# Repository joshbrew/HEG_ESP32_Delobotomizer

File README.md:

# HEG ESP32 - Delobotomizer Edition

Official repository for the HEGduino V2 Delobotomizer firmware, software, and designs.

### [WebApp: Brains@Play](https://app.brainsatplay.com)
- This will replace the original software and is MUCH more robust, we are still doing a lot of legwork to get all of the quality of life features we want into it but welcome to the new multi-bci community framework for the web! 
- Chrome only for desktop, works on Android and in VR. 
- Find the install button via the settings button in the top right of the browser.
### [Getting Started (click me)](https://github.com/moothyknight/HEG_ESP32_Delobotomizer/blob/main/Guides/GettingStarted.md)
### [Updating Your Device](https://github.com/moothyknight/HEG_ESP32_Delobotomizer/blob/main/Guides/Updating.md)
### [Whitepaper](https://github.com/moothyknight/HEG_ESP32_Delobotomizer/blob/main/Guides/Open%20Source%20HEG_FNIRS%20Whitepaper.pdf)
### [Old Progressive Web App (no longer updated)](https://hegalomania.netlify.app) 
- Original webapp demo, use via Chrome for Serial USB support. Use BLE mode if the USB device is not recognized in browser, this is a known issue. If that fails use the web server with the device in WiFi mode.

### If your browser won't identify the USB connection, try installing the VCP for Windows (or Mac) drivers here: https://www.silabs.com/developers/usb-to-uart-bridge-vcp-drivers

## Firmware

The Firmware folder contains a .bin file that you can use via the on-board web interface to update the device. There are Arduino libraries and firmware code files for custom code, you will need the ESP32 module additionally for Arduino.

Simply connect to the wifi network named "My_HEG" when the device is powered up with password "12345678"

In your preferred browser, enter "192.168.4.1" into the address bar. You should see an interface show up. Click on the Update button to go to the update page.

Now follow the instructions on screen to browse for the .bin folder that you may download from this repo. Wait for it to finish uploading then reconnect to the HEG after that's taken care of if it does not do it automatically. Voila!

## Progressive Web App (WIP): https://hegalomania.netlify.app

Our new preferred method for using the HEG, a state of the art Progressive Web App! 

Open this link to use your HEG in a Chrome browser or Android for instant access to using your device. This is being updated to a React app with a more familiar UI and a more concise code base to expand from.

You may install it locally on desktop or mobile as well just like any app and create desktop shortcuts. For desktop open the settings bar in Chrome and click "Install HEG Alpha." The USB mode only works in chrome right now as it is a development feature. You can enable this feature by going to chrome://flags and enabling the "Experimental Web Platform features" flag. For mobile it should prompt you to install, if not find the install button in your chrome settings menu on mobile.

## Boot routine

The newer firmware contains a new boot-up routine for making it easier to identify streaming modes on the device. It will flash when powered up to indicate which mode it's in.

On boot:
* Two fast blinks: BLE mode
* Three fast blinks: WIFI mode
* Four fast blinks: Bluetooth Classic (Serial) mode

The button on the newer devices puts your device to sleep. There will be a switch added next to control device settings.

Since your device is covered in tape this will help you find the reset button if I didn't mark it for you:

## Device Commands (accessible via app (Send Command button) or serial monitor)

* 't' - Turn sensor ON (automatic)
* 'f' - Turn sensor OFF, device will go to sleep after 10min of inactivity
* 'b' - BLE mode toggle. Toggles back to WiFi mode.
* 'B' - Bluetooth Serial toggle. Toggles back to WiFi mode.
* 'W' - Reset WiFi credentials (if it won't connect to your router)
* 'R' - Reboot device
* 'S' - Enter deep sleep mode e.g. to save battery
* 'u' - USB only output mode (no wireless signals)
* 'o' - Fast output mode (<20 byte packets for Android Web BLE)
* 'L' - External LED mode, configured for pins 12 and 14 to run LEDs and be sampled.
* 'N' - Toggle SPO2 output (experimental, not working properly yet)
* 'D' - Toggle Debug output (for using Arduino's graphing)
* 'e' - Toggle exposure settings: slow, fast, and default. default has the slowest output rate but samples faster than slow mode with more averaging.
* 'l' - Toggle LED protocols in this order: Ambient,IR,2 IR (AMBIENT, LED2, LED1+2); Red,IR,2 IR (LED3, LED2, LED1+2), Red = IR (LED1, LED2, AMB), or Default (LED3,LED2,AMBIENT)
* 'X' - DC filter toggle
* 'F' - Digital filter toggle
Note, use the first setting with the command 'l' if your red LED is underperforming. This will make the software compare Ambient and IR, and optional both IR LEDs for extra strength. For some reason the red output is not as consistent for some people.

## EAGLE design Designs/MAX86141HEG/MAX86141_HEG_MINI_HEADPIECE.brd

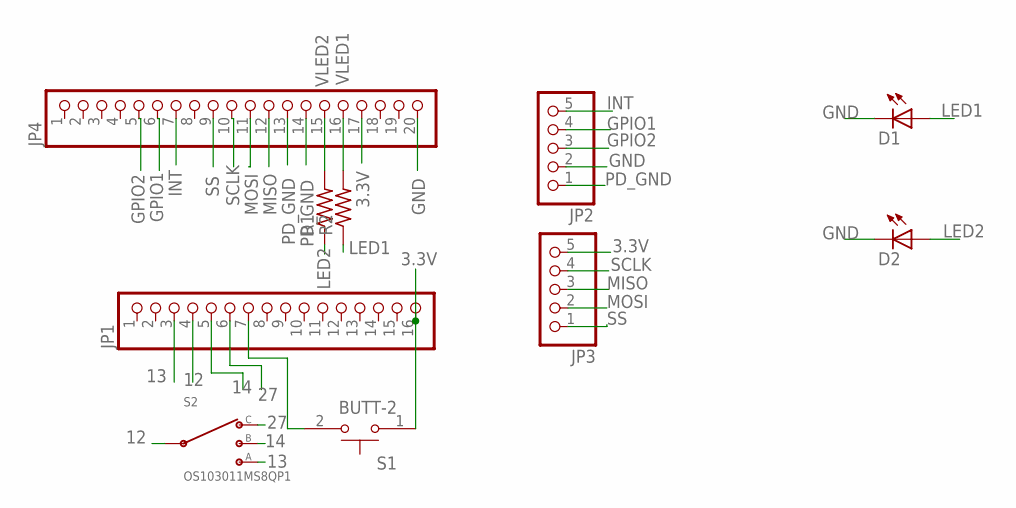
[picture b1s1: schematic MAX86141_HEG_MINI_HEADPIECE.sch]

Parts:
D1, D2: LED1206; LED-1206
JP1: PINHD-1X16; 1X16
JP2, JP3: PINHD-1X5; 1X05
JP4: PINHD-1X20; 1X20
R1, R2: R-US_0204/5; 0204/5
S1: BUTT-2; SW_BUTT-2
S2: OS103011MS8QP1; OS102011MS8QP1

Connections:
3.3V: JP1.16, JP3.5, JP4.17, S1.1
12: JP1.4, S2.2 (C)
13: JP1.3, S2.1
14: JP1.5, S2.3 (2)
27: JP1.6, S2.4 (3)
GND: D1.C, D2.C, JP2.2, JP4.20
GPIO1: JP2.4, JP4.6
GPIO2: JP2.3, JP4.5
INT: JP2.5, JP4.7
LED1: D1.A, R2.1
LED2: D2.A, R1.1
MISO: JP3.3, JP4.12
MOSI: JP3.2, JP4.11
unnamed: JP1.7, S1.2
PD_GND: JP2.1, JP4.13, JP4.14
SCLK: JP3.4, JP4.10
SS: JP3.1, JP4.9
VLED1: JP4.16, R2.2
VLED2: JP4.15, R1.2

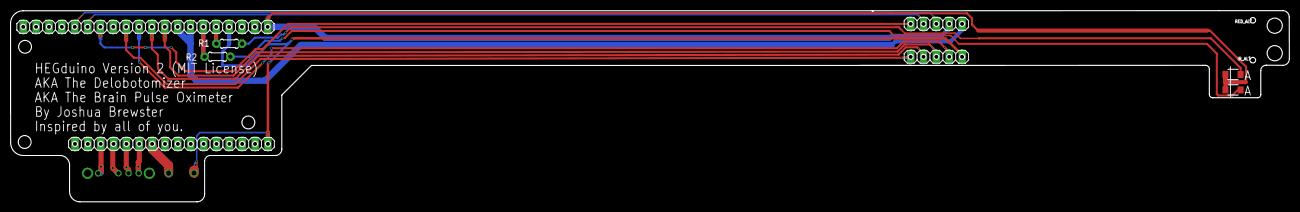
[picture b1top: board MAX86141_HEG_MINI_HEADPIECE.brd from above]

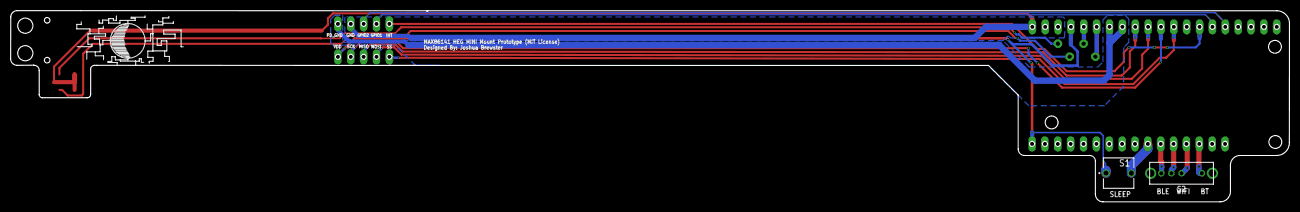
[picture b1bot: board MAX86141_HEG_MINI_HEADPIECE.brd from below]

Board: 2 copper layers, 252.5 x 37.7 mm, 10 parts (2 on the bottom side), 19 nets.

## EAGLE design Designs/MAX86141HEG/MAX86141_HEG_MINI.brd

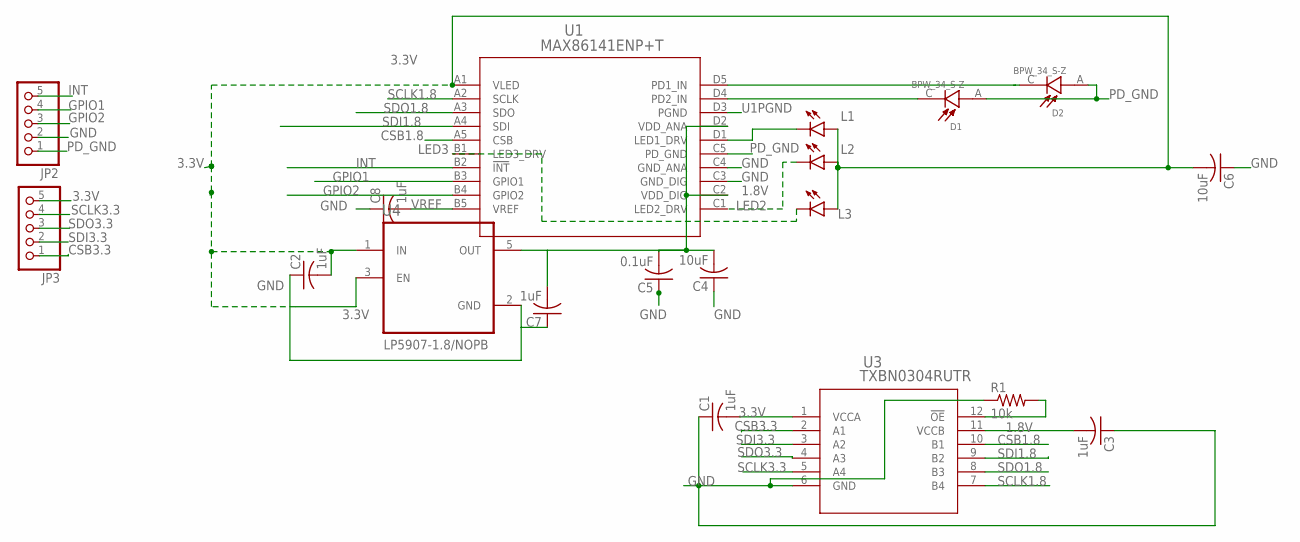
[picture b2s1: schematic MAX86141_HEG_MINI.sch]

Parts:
C1, C2, C3, C7, C8: 1uF; C0402
C4, C6: 10uF; C0402
C5: 0.1uF; C0402
D1, D2: BPW_34_S-Z; DIO_BPW_34_S-Z
JP2, JP3: PINHD-1X5; 1X05
L1, L2, L3: LEDCHIPLED_1206; CHIPLED_1206
R1: 10k; R0402
U1: MAX86141ENP+T; 21-100134_N201A2-1_MXM
U3: TXBN0304RUTR; RUT12
U4: LP5907MFX-3.3/NOPB; SOT95P280X145-5N

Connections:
1.8V: C3.2, C4.2, C5.2, C7.2, U1.C2 (VDD_DIG), U1.D2 (VDD_ANA), U3.11 (VCCB), U4.5 (OUT)
3.3V: C1.2, C2.2, C6.2, JP3.5, L1.A, L2.A, L3.A, U1.A1 (VLED), U3.1 (VCCA), U4.1 (IN), U4.3 (EN)
CSB1.8: U1.A5 (CSB), U3.10 (B1)
CSB3.3: JP3.1, U3.2 (A1)
GND: C1.1, C2.1, C3.1, C4.1, C5.1, C6.1, C7.1, C8.1, JP2.2, R1.1, U1.C3 (GND_DIG), U1.C4 (GND_ANA), U3.6 (GND), U4.2 (GND)
GPIO1: JP2.4, U1.B3 (GPIO1)
GPIO2: JP2.3, U1.B4 (GPIO2)
INT: JP2.5, U1.B2 (!INT)
LED1: L1.C, U1.D1 (LED1_DRV)
LED2: L2.C, U1.C1 (LED2_DRV)
LED3: L3.C, U1.B1 (LED3_DRV)
OE: R1.2, U3.12 (!OE)
PD1_IN: D2.C, U1.D5 (PD1_IN)
PD2_IN: D1.C, U1.D4 (PD2_IN)
PD_GND: D1.A, D2.A, JP2.1, U1.C5 (PD_GND)
SCLK1.8: U1.A2 (SCLK), U3.7 (B4)
SCLK3.3: JP3.4, U3.5 (A4)
SDI1.8: U1.A4 (SDI), U3.9 (B2)
SDI3.3: JP3.2, U3.3 (A2)
SDO1.8: U1.A3 (SDO), U3.8 (B3)
SDO3.3: JP3.3, U3.4 (A3)
U1PGND: U1.D3 (PGND)
VREF: C8.2, U1.B5 (VREF)

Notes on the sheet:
LP5907-1.8/NOPB

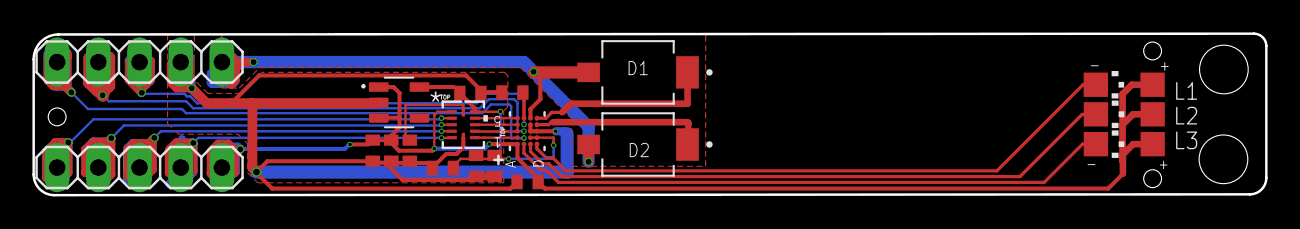
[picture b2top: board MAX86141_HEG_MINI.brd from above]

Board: 2 copper layers, 76.0 x 10.0 mm, 19 parts (0 on the bottom side), 22 nets.

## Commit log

2020-10-15 fixes in design I'm testing
2020-10-21 new whitepaper
2020-10-24 convenience features, BLE in extension
2020-10-24 bin file updated
2020-10-28 quality control
2020-10-30 needed some data in ther
2020-10-31 boids update
2020-10-31 Rename README.txt to README.md
2020-11-02 fixes to firmware
2020-12-02 edits
2020-12-04 firmware fix
2020-12-07 Create txt
2020-12-08 updates,
2020-12-17 updated BOM
2020-12-30 updates/another fix for boot routine
2020-12-30 rename/move
2021-01-22 implement IIR filters (no more AC noise)
2021-01-23 BLE fix, filter tweak
2021-01-23 fix date on index page
2021-01-23 Revert "fix date on index page"
    This reverts commit fccd3de28d8638ee936c8c1eb6b53d1d49f046b3.
2021-01-23 Revert "Revert "fix date on index page""
    This reverts commit 6bfa90bcc4cf0c51ec1b0ffc417e70c4e8824c86.
2021-03-03 formatting fix
2021-03-17 brighter red led
2021-04-24 push
2021-04-24 minor fixes (reset and sleep command shuts sensor off correctly)
2021-04-27 added 'e' and 'l' commands to tweak exposure and LED settings.
2021-04-27 updated bin
2021-04-29 additional LED mode with 'l' to set red as ambient. Testing BLE OTA also
2021-05-09 enable die temp reading by default in last position
2021-05-09 update with temp readings
2021-06-07 uploaded dxf (will be updating boards soon however)
2021-06-08 quality improvements to design (hopefully)
2021-06-17 headpiece update with switches
2021-06-20 more holes for switch mount
2021-07-08 reverted breakout board (trace spacing too narrow)
2021-10-02 updated firmware
2021-11-08 pushed firmware updates
2021-11-29 replaced update files, switch actually will work now (for newest boards with it installed)
2022-01-26 firmware tweaks + IR/Amb version (no Red LED by default)

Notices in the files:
Designs/MAX86141HEG/MAX86141_HEG_MINI.brd:
MAX86141 HEG MINI Prototype (MIT License)
Joshua Brewster - MIT License
Designs/MAX86141HEG/MAX86141_HEG_MINI_HEADPIECE.brd:
MAX86141 HEG MINI Mount Prototype (MIT License)
HEGduino Version 2 (MIT License)
parts and their libraries:
MAX86141: COPYRIGHT: Copyright (C) 2018 Accelerated Designs. All rights reserved
